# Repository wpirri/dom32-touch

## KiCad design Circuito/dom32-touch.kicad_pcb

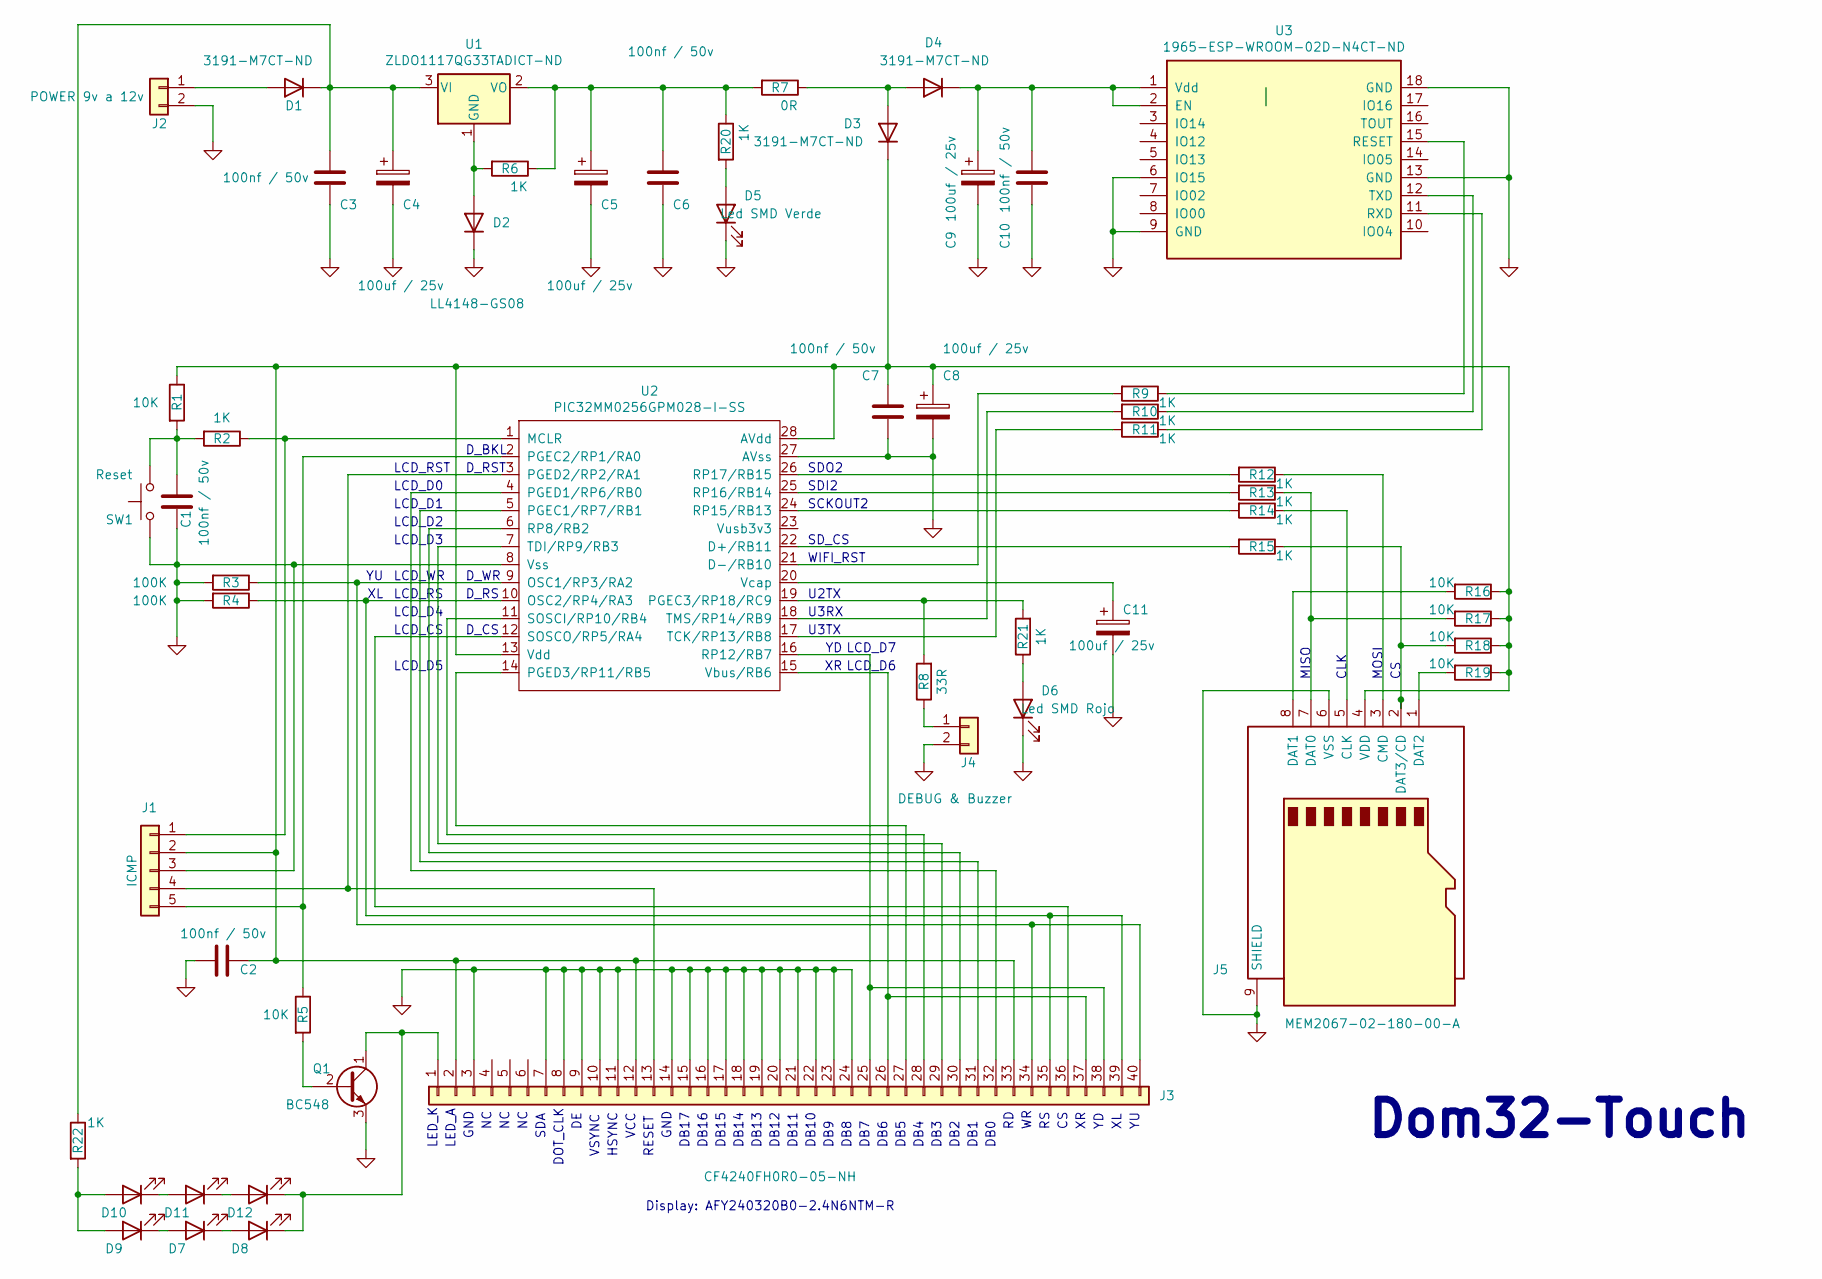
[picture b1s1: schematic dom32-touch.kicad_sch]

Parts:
C1, C2, C3, C6, C7, C10: 100nf / 50v; C_0805_2012Metric_Pad1.18x1.45mm_HandSolder
C4, C5, C8, C9, C11: 100uf / 25v; CP_Elec_6.3x7.7
D1, D3, D4: 3191-M7CT-ND; D_SMA
D2: LL4148-GS08; D_SOD-128
D5: Led SMD Verde; D_0805_2012Metric_Pad1.15x1.40mm_HandSolder
D6: Led SMD Rojo; D_0805_2012Metric_Pad1.15x1.40mm_HandSolder
D7, D8, D9, D10, D11, D12: Led SMD Azul; D_0805_2012Metric_Pad1.15x1.40mm_HandSolder
J1: Poste X 5; PinHeader_1x05_P2.54mm_Vertical
J2: 277-1667-ND; TerminalBlock_Phoenix_PT-1,5-2-5.0-H_1x02_P5.00mm_Horizontal
J3: CF4240FH0R0-05-NH; TE_4-1734839-0_1x40-1MP_P0.5mm_Horizontal
J4: DEBUG & Buzzer; PinHeader_1x02_P2.54mm_Vertical
J5: MEM2067-02-180-00-A; microSD_HC_Wuerth_693072010801
Q1: BC548; SOT-23
R1, R5, R16, R17, R18, R19: 10K; R_0805_2012Metric_Pad1.20x1.40mm_HandSolder
R2, R6, R9, R10, R11, R12, R13, R14, R15, R20, R21, R22: 1K; R_0805_2012Metric_Pad1.20x1.40mm_HandSolder
R3, R4: 100K; R_0805_2012Metric_Pad1.20x1.40mm_HandSolder
R7: 0R; R_0805_2012Metric_Pad1.20x1.40mm_HandSolder
R8: 33R; R_0805_2012Metric_Pad1.20x1.40mm_HandSolder
SW1: TactSwitch; SW_Push_1P1T_NO_6x6mm_H9.5mm
U1: ZLDO1117QG33TADICT-ND; SOT-223-3_TabPin2
U2: PIC32MM0256GPM028-I-SS; SSOP-28_5.3x10.2mm_P0.65mm
U3: 1965-ESP-WROOM-02D-N4CT-ND; ESP-WROOM-02

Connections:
GND: C1.2, C2.1, C3.2, C4.2, C5.2, C6.2, C7.2, C8.2, C9.2, C10.2, C11.2, D2.1 (K), D5.1 (K), D6.1 (K), J1.3, J2.2, J3.3, J3.7, J3.8, J3.9, J3.10, J3.11, J3.14, J3.15, J3.16, J3.17, J3.18, J3.19, J3.20, J3.21, J3.22, J3.23, J3.24, J4.2, J5.6 (VSS), J5.9 (SHIELD), Q1.3 (E), R3.2, R4.2, SW1.1, U2.8 (Vss), U2.27 (AVss), U3.6 (IO15), U3.9 (GND), U3.13 (GND), U3.18 (GND)
unnamed: C1.1, R1.2, R2.2, SW1.2
unnamed: D1.2 (A), J2.1
unnamed: C3.1, C4.1, D1.1 (K), R22.1, U1.3 (VI)
unnamed: D2.2 (A), R6.2, U1.1 (GND)
unnamed: D3.2 (A), D4.2 (A), R7.1
unnamed: C2.2, C7.1, C8.1, D3.1 (K), J1.2, J3.2, J3.12, J3.33, J5.4 (VDD), R1.1, R16.1, R17.1, R18.1, R19.1, U2.13 (Vdd), U2.28 (AVdd)
unnamed: C9.1, C10.1, D4.1 (K), U3.1 (Vdd), U3.2 (EN)
unnamed: D5.2 (A), R20.2
unnamed: D6.2 (A), R21.1
unnamed: D7.2 (A), D9.1 (K)
unnamed: D7.1 (K), D8.2 (A)
unnamed: D9.2 (A), D10.2 (A), R22.2
unnamed: D10.1 (K), D11.2 (A)
unnamed: D11.1 (K), D12.2 (A)
unnamed: D8.1 (K), D12.1 (K), J3.1, Q1.1 (C)
unnamed: J1.1, R2.1, U2.1 (MCLR)
unnamed: J1.4, J3.13, U2.3 (PGED2/RP2/RA1)
unnamed: J1.5, R5.1, U2.2 (PGEC2/RP1/RA0)
unnamed: J3.25, J3.38, U2.16 (RP12/RB7)
unnamed: J3.26, J3.37, U2.15 (Vbus/RB6)
unnamed: J3.27, U2.14 (PGED3/RP11/RB5)
unnamed: J3.28, U2.11 (SOSCI/RP10/RB4)
unnamed: J3.29, U2.7 (TDI/RP9/RB3)
unnamed: J3.30, U2.6 (RP8/RB2)
unnamed: J3.31, U2.5 (PGEC1/RP7/RB1)
unnamed: J3.32, U2.4 (PGED1/RP6/RB0)
unnamed: J3.34, J3.40, R3.1, U2.9 (OSC1/RP3/RA2)
unnamed: J3.35, J3.39, R4.1, U2.10 (OSC2/RP4/RA3)
unnamed: J3.36, U2.12 (SOSCO/RP5/RA4)
unnamed: J4.1, R8.1
unnamed: J5.5 (CLK), R14.1
unnamed: J5.3 (CMD), R12.1
unnamed: J5.7 (DAT0), R13.1, R17.2
unnamed: J5.8 (DAT1), R16.2
unnamed: J5.1 (DAT2), R19.2
unnamed: J5.2 (DAT3/CD), R15.1, R18.2
unnamed: Q1.2 (B), R5.2
unnamed: C5.1, C6.1, R6.1, R7.2, R20.1, U1.2 (VO)
unnamed: R15.2, U2.22 (D+/RB11)
unnamed: R9.2, U2.21 (D-/RB10)
unnamed: R8.2, R21.2, U2.19 (PGEC3/RP18/RC9)
unnamed: R14.2, U2.24 (RP15/RB13)
unnamed: R13.2, U2.25 (RP16/RB14)
unnamed: R12.2, U2.26 (RP17/RB15)
unnamed: R11.2, U2.17 (TCK/RP13/RB8)
unnamed: R10.2, U2.18 (TMS/RP14/RB9)
unnamed: C11.1, U2.20 (Vcap)
unnamed: R9.1, U3.15 (RESET)
unnamed: R11.1, U3.11 (RXD)
unnamed: R10.1, U3.12 (TXD)

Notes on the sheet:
LCD_D2
LCD_D5
D_BKL
MISO
DB7
U2TX
VSYNC
D_CS
DB12
LCD_CS
DB11
SCKOUT2
CLK
DB5
DB0
LCD_D7
DB16
D_RST
Dom32-Touch
DB13
DB9
LED_A
SDA
LED_K
GND
D_WR
DB8
LCD_RS
SDO2
DB14
U3TX
DOT_CLK
DB2
DB6
WIFI_RST
LCD_D6
LCD_D4
LCD_D1
DB15
LCD_D3

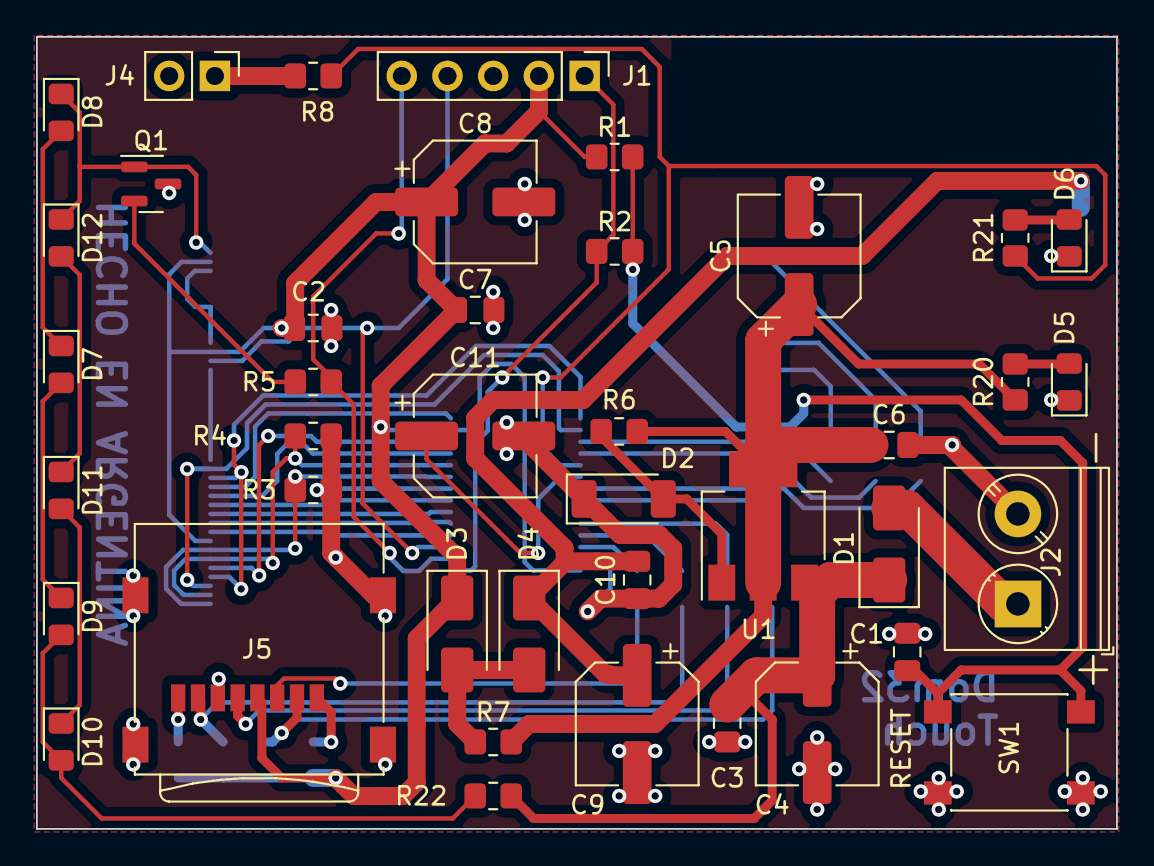
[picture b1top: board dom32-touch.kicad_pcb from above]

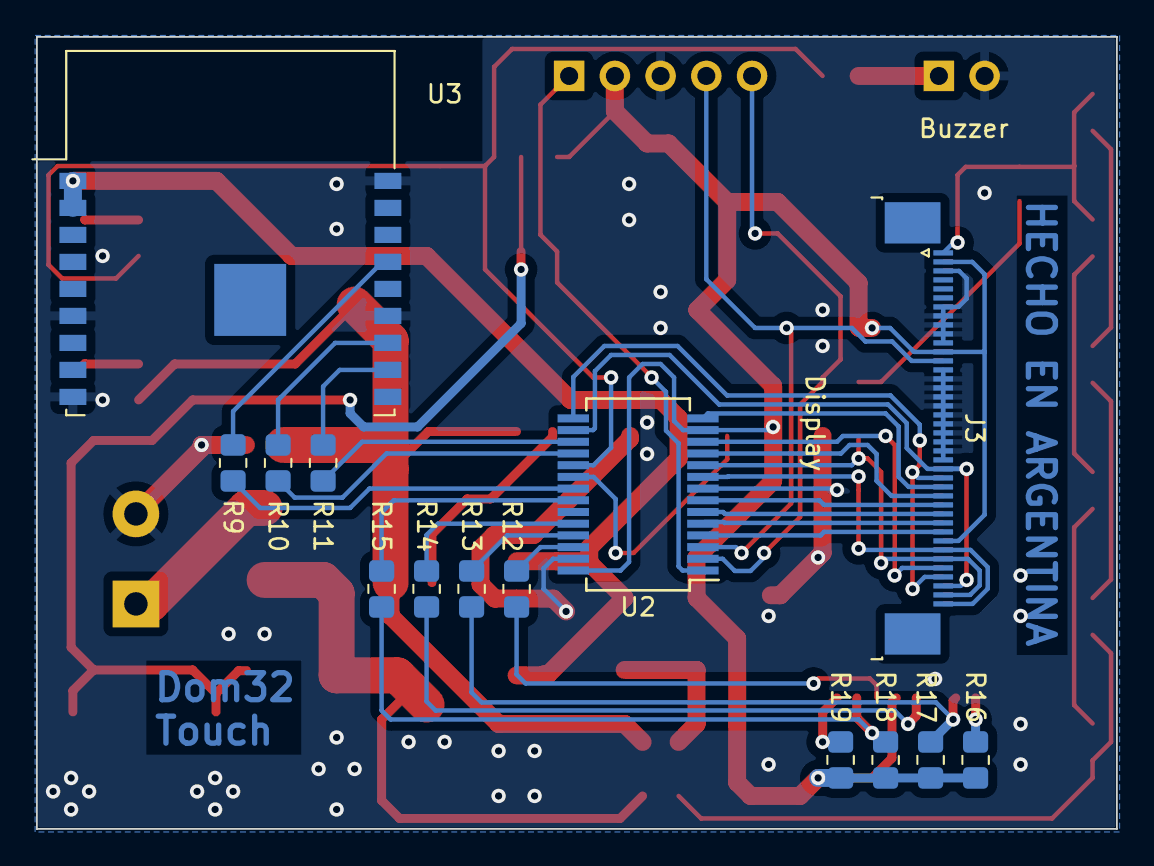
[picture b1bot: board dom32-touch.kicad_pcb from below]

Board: 2 copper layers, 60.0 x 44.0 mm, 55 parts (14 on the bottom side), 51 nets.

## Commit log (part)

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2024-09-28 Timer y leds Ok
    Timer y leds Ok
2024-09-28 Log al serial Ok
    Log al serial Ok
2024-10-03 Update NOTAS.txt
    Se agrega información del display
2024-10-04 SD Ok
    SD Ok
2024-10-04 Se mueve el circuito de directorio
    Se mueve el circuito de directorio
2024-10-04 Bus SPI Compartido
    Bus SPI Compartido
2024-10-05 Problema en init del display
    Problema en init del display
2024-10-10 No funciona
    El display utilizado necesita alimentarse con 5v y las señales en el mismo valor. El uso de open collector con resistencias de 10k a 5v no alcanzó
2024-10-12 Pinta medio display
    Pinta medio display
2024-10-12 Display Ok
    Display Ok
2024-10-12 Sin delays
    Sin delays
2024-10-14 Texto
    Texto
2024-10-15 Touch codificado pero no funciona
    Touch codificado pero no funciona
2024-10-15 Touch medio avanzado
    Touch medio avanzado
2024-10-15 Touch casi anda
    Touch casi anda
2024-10-15 Touch Ok
    Touch Ok
2024-10-16 Touch mejorado
    Touch mejorado
2024-10-16 Nacimiento de botones
    Nacimiento de botones
2024-10-16 Logica de botones
    Logica de botones
2024-10-16 Texto centrado en botones
    Texto centrado en botones
2024-10-18 Boton con icono
    Boton con icono
2024-10-30 Agregado de modulo wifi
    Agregado de modulo wifi
2024-10-30 Inicio en control
    Inicio en control
2024-10-30 Config Ok
    Config Ok
2024-10-31 Screen home desde archivo OK
    Screen home desde archivo OK
2024-11-01 Inicio con power
    Inicio con power
2024-11-01 El color de la transparencia cambia de blanco a negro
    El color de la transparencia cambia de blanco a negro
2024-11-02 Implementacion de funcion switch
    Implementacion de funcion switch
2024-11-02 Prevencion de download no solicitado
    Prevencion de download no solicitado
2024-11-03 MAC Ok
    MAC Ok
2024-11-03 Configuracion de wifi
    Configuracion de wifi
2024-11-04 Downloads
    Downloads
2024-11-05 Beep
    Beep
2024-11-06 Seccion config
    Seccion config
2024-11-07 Correcciones en download
    Correcciones en download
2024-11-07 Update
    Update
2024-11-08 Inicio acelerado
    Inicio acelerado
2024-11-18 Adaptacion display de Orieny Display
    Adaptacion display de Orieny Display
2024-11-19 Display Orient en 8 Bit
    Display Orient en 8 Bit
2024-11-20 Move
    Move
2024-11-20 Inicio Placa
    Inicio Placa
2024-11-21 Circuito Impreso
    Circuito Impreso
2024-11-22 Brillo y Screen Saver
    Brillo y Screen Saver
2024-11-22 DRC Ok
    DRC Ok
2024-11-22 Niveles de brillo y scrren saver por config
    Niveles de brillo y scrren saver por config
2024-11-26 Mejoras en la inicializacion WiFi
    Mejoras en la inicializacion WiFi
2024-11-26 Generacion de placa para cotizacion
    Generacion de placa para cotizacion
2024-11-26 Programa booteable
2024-11-28 Mejoras en WiFi, Http y Upgrade
    Mejoras en WiFi, Http y Upgrade
2024-12-06 Equiparacion de fuentes
    Equiparacion de fuentes
2024-12-18 Fabricacion
    Fabricacion
2024-12-18 Correccion en lectura de configuracion
    Correccion en lectura de configuracion
2024-12-18 Soporte
    Soporte
2024-12-22 Correccion de parametros de configuracion
    Correccion de parametros de configuracion
2024-12-22 Menu para comedor
2024-12-22 Ajustes
    Ajustes
2024-12-22 Adaptador
    Adaptador
2024-12-26 Correcciones
    Se extiende el tamaño para armar el GET
    Se corrige el screen saver a la vuelta del offline
    Se agrega offline en respuesta con error
2024-12-26 Botones mas grandes y bordes mas gruesos
    Botones mas grandes y bordes mas gruesos
2024-12-27 Efecto de sombra
    Se agrega un pequeño oscurecimiento de la pantalla al presionar un boton con un comando
2024-12-30 Correccion de download
    Correccion de download
2025-01-02 Mejoras en Upload
    Mejoras en Upload
2025-01-02 Mejoras en botones y opcion debug
    Mejoras en botones y opcion debug
2025-01-02 Tabla de colores
    Tabla de colores
2025-01-02 Optimizacion
    Optimizacion
2025-01-04 Nuevas pantallas
    Nuevas pantallas
2025-01-04 Correcciones después de download
    Después de un download se desconectaba el dispositivo y reconectaba luego de reintentos
2025-01-09 Correccion en manejo de comunicacion
    Correccion en manejo de comunicacion
2025-01-10 Pantalla de offline
    Pantalla de offline
2025-02-01 Actualizacion
    Actualizacion
2025-03-30 reorganizacion de microsd
    reorganizacion de microsd
2025-03-30 Mas opciones de botones
    Mas opciones de botones
2025-04-23 Correcciones en WiFi
    Correcciones en WiFi
2025-06-06 Soporte para display SPI
    Soporte para display SPI
2025-06-06 Mas Displays
    Mas Displays
2025-06-12 Configuracion de pantallas de dispositivos touch
    Configuracion de pantallas de dispositivos touch
2025-06-12 Correcciones minimas
    Correcciones minimas
2025-06-13 Download de litsado de archivos Ok
    Download de litsado de archivos Ok
2025-06-13 Offline mientras actualiza
    Offline mientras actualiza
2025-06-14 Implementado
    Implementado
2025-06-16 Reorganización de archivos
    Reorganización de archivos
2025-06-16 Corrección de menu de configuración
    Corrección de menu de configuración
2025-06-21 Acomodando archivos
    Acomodando archivos
2025-06-21 Listado de descarga
    Corrección en interpretación de listado de descarga
2025-06-26 Borde de botones mas grueso
    Borde de botones mas grueso
2025-06-27 RTCC
    RTCC
2025-07-23 Investigacion de funcionalidad para PNG
    Investigacion de funcionalidad para PNG
2025-07-23 Bastidor completo
    Bastidor completo
2025-10-04 Download de cualquier tipo de archivo
    Download de cualquier tipo de archivo
2025-10-09 Control de integridad de archivo bajado
    Control de integridad de archivo bajado
2025-12-14 Contador de errores de recepcion no se usa
    Contador de errores de recepcion no se usa
2026-02-21 Se agrega el port en la configuración de la central
    Se agrega el port en la configuración de la central
2026-05-30 Quitando basura
    Quitando basura
2026-05-30 Firmware rediseñado
    Firmware rediseñado
2026-05-30 Se agrega lectura de configuracion
    Se agrega lectura de configuracion
2026-05-31 Inicializacion
    Inicializacion
2026-06-01 Config Screen
    Config Screen
2026-06-02 Pantalla de configuracion
    Pantalla de configuracion
2026-06-02 Query al Host
    Query al Host
2026-06-03 QueryHost Corregido
    QueryHost Corregido
2026-06-03 Deteccion on line
    Deteccion on line
2026-06-03 Comandos de botones
    Comandos de botones
2026-06-03 Correccion en el Close del query al host
    Correccion en el Close del query al host
2026-06-05 Download
    Download
2026-06-07 Primera parte de file download
    Primera parte de file download
2026-06-10 Download Ok
    Download Ok
2026-06-11 Profile Booteable
    Profile Booteable, Screen Saver, Datos de compilacion al arrancar
2026-06-11 COnfiguracion remota
    COnfiguracion remota
2026-06-20 Correccion de overflow
    Correccion de overflow
2026-06-20 Me aseguro de la desconexion
    Me aseguro de la desconexion
2026-06-22 Mas tiempo de conexión
    Mas tiempo de conexión
